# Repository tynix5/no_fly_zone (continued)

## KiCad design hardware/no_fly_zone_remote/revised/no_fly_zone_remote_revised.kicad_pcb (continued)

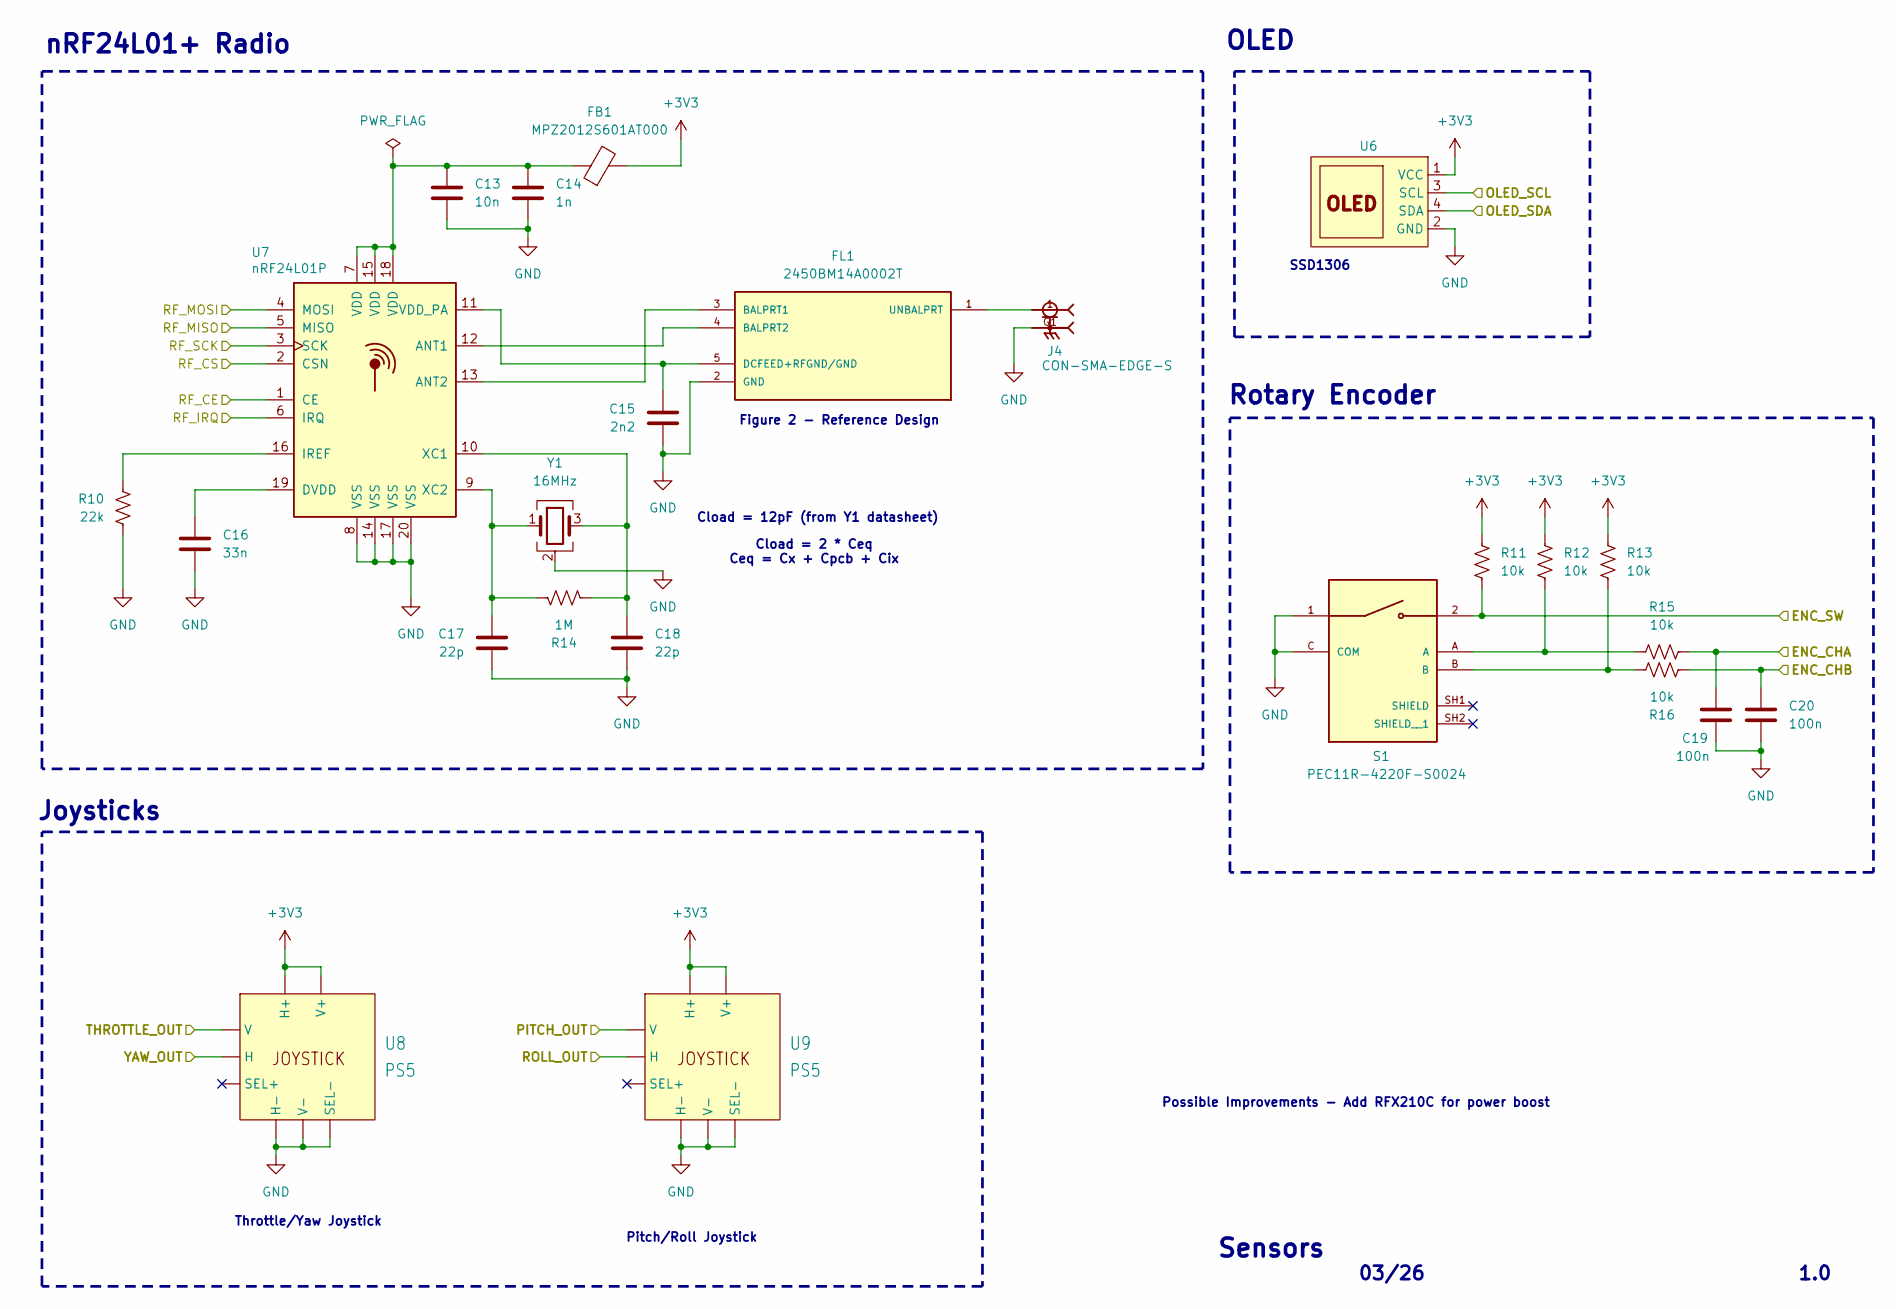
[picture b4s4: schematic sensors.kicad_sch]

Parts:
C13: 10n; C_0402_1005Metric
C14: 1n; C_0402_1005Metric
C15: 2n2; C_0402_1005Metric
C16: 33n; C_0402_1005Metric
C17, C18: 22p; C_0402_1005Metric
C19, C20: 100n; C_0805_2012Metric
FB1: MPZ2012S601AT000; R_0805_2012Metric
FL1: 2450BM14A0002T; FIL_2450BM14A0002T
J4: CON-SMA-EDGE-S; RFSOLUTIONS_CON-SMA-EDGE-S
R10: 22k; R_0402_1005Metric
R11, R12, R13, R15, R16: 10k; R_0805_2012Metric
R14: 1M; R_0402_1005Metric
S1: PEC11R-4220F-S0024; XDCR_PEC11R-4220F-S0024
U6: PinHeader_1x04_P2.54mm_Vertical
U7: nRF24L01P; QFN-20-1EP_4x4mm_P0.5mm_EP2.5x2.5mm
U8, U9: PS5; PS5_Joystick
Y1: 16MHz; XTAL_ABM8AIG-16.000MHZ-12-2Z-T3

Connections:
+3V3: FB1.2, R11.1, R12.1, R13.1, U6.1 (VCC), U8.3 (H+), U8.3' (V+), U9.3 (H+), U9.3' (V+); also elsewhere on the board
/MCU/ADC1_IN7: U9.2' (V); also elsewhere on the board
/MCU/ADC1_IN8: U9.2 (H); also elsewhere on the board
/MCU/ADC1_IN9: U8.2' (V); also elsewhere on the board
/MCU/ADC1_IN16: U8.2 (H); also elsewhere on the board
/MCU/ENC_SW: R11.2, S1.2; also elsewhere on the board
/MCU/I2C1_SCL: U6.3 (SCL); also elsewhere on the board
/MCU/I2C1_SDA: U6.4 (SDA); also elsewhere on the board
/MCU/RF_CE: U7.1 (CE); also elsewhere on the board
/MCU/RF_CS: U7.2 (CSN); also elsewhere on the board
/MCU/RF_IRQ: U7.6 (IRQ); also elsewhere on the board
/MCU/SPI1_MISO: U7.5 (MISO); also elsewhere on the board
/MCU/SPI1_MOSI: U7.4 (MOSI); also elsewhere on the board
/MCU/SPI1_SCK: U7.3 (SCK); also elsewhere on the board
/MCU/TIM2_CH1: C19.1, R15.2; also elsewhere on the board
/MCU/TIM2_CH2: C20.1, R16.1; also elsewhere on the board
GND: C13.2, C14.2, C15.2, C16.2, C17.2, C18.2, C19.2, C20.2, FL1.2 (GND), J4.G1, J4.G2, J4.G3, J4.G4, R10.2, S1.1, S1.C (COM), U6.2 (GND), U7.8 (VSS), U7.14 (VSS), U7.17 (VSS), U7.20 (VSS), U8.1 (H-), U8.1' (V-), U8.c (SEL-), U9.1 (H-), U9.1' (V-), U9.c (SEL-), Y1.2 (G), Y1.4 (G); also elsewhere on the board
unnamed: C13.1, C14.1, FB1.1, U7.7 (VDD), U7.15 (VDD), U7.18 (VDD)
unnamed: FL1.3 (BALPRT1), U7.13 (ANT2)
unnamed: FL1.4 (BALPRT2), U7.12 (ANT1)
unnamed: C15.1, FL1.5 (DCFEED+RFGND/GND), U7.11 (VDD_PA)
unnamed: FL1.1 (UNBALPRT), J4.1
unnamed: R12.2, R15.1, S1.A
unnamed: R13.2, R16.2, S1.B
unnamed: C16.1, U7.19 (DVDD)
unnamed: R10.1, U7.16 (IREF)
unnamed: C18.1, R14.1, U7.10 (XC1), Y1.3
unnamed: C17.1, R14.2, U7.9 (XC2), Y1.1

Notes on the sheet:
03/26
Figure 2 - Reference Design
nRF24L01+ Radio
SSD1306
Rotary Encoder
Cload = 2 * Ceq Ceq = Cx + Cpcb + Cix
Joysticks
Cload = 12pF (from Y1 datasheet)
OLED
1.0
Sensors
Throttle/Yaw Joystick
Pitch/Roll Joystick
Possible Improvements - Add RFX210C for power boost

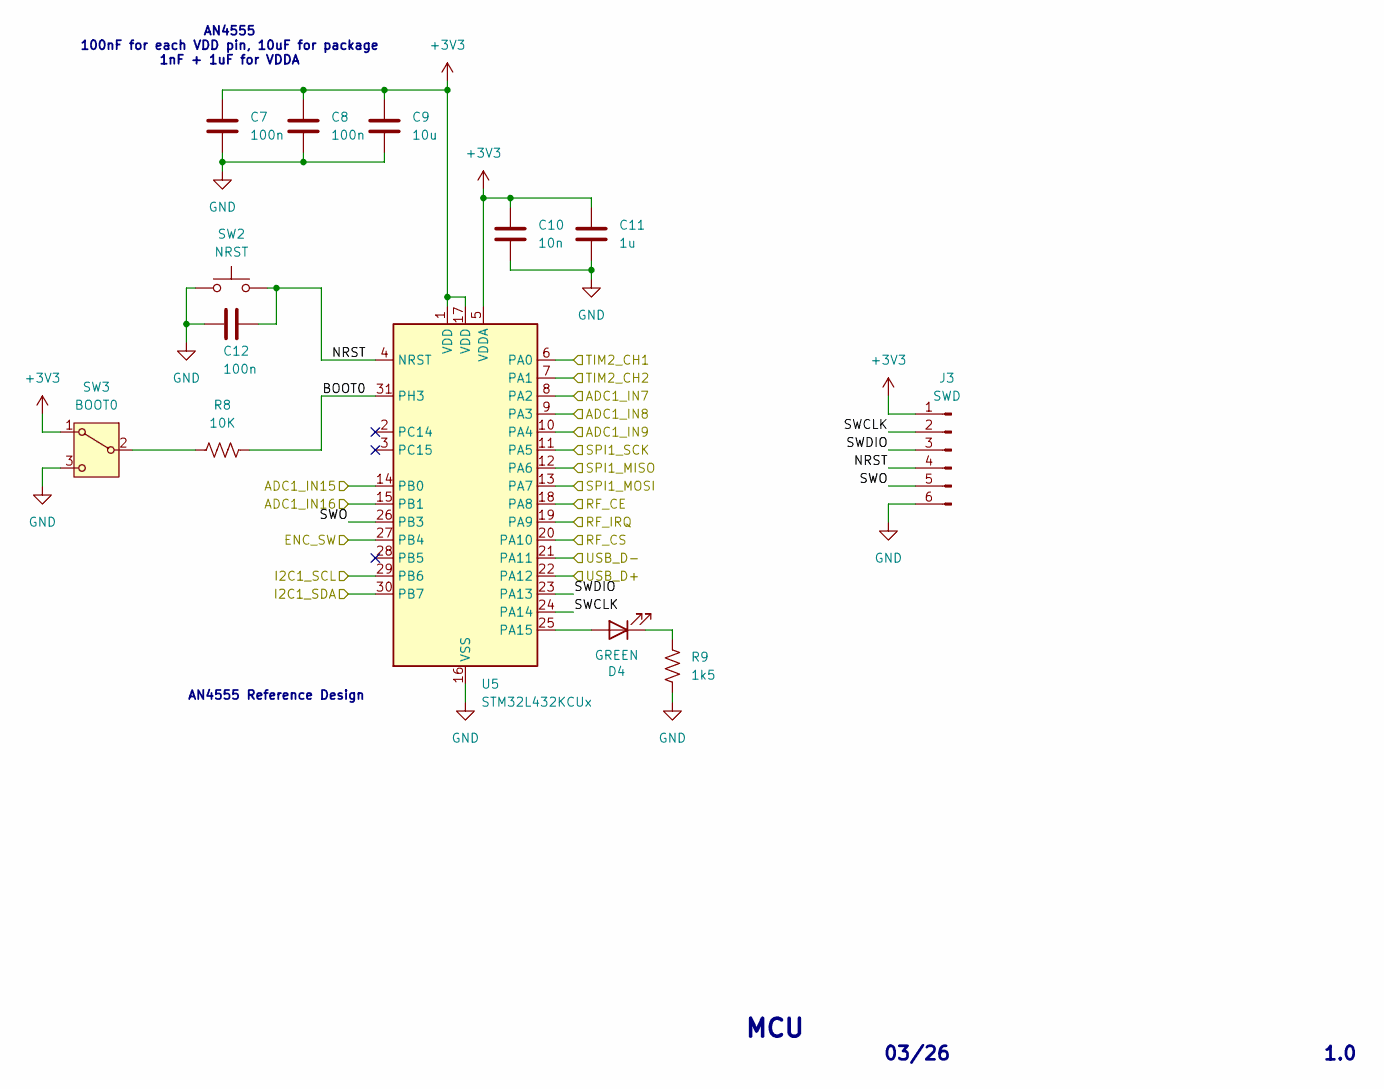
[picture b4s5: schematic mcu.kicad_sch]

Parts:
C7, C8, C12: 100n; C_0805_2012Metric
C9: 10u; C_0805_2012Metric
C10: 10n; C_0805_2012Metric
C11: 1u; C_0805_2012Metric
D4: GREEN; LED_0805_2012Metric
J3: SWD; PinHeader_1x06_P2.54mm_Vertical
R8: 10K; R_0805_2012Metric
R9: 1k5; R_0805_2012Metric
SW2: NRST; SW_SPST_TL3305A
SW3: BOOT0; SW_SPDT_PCM12
U5: STM32L432KCUx; QFN-32-1EP_5x5mm_P0.5mm_EP3.45x3.45mm

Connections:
+3V3: C7.1, C8.1, C9.1, C10.1, C11.1, J3.1, SW3.1 (A), U5.1 (VDD), U5.5 (VDDA), U5.17 (VDD); also elsewhere on the board
/MCU/ADC1_IN7: U5.8 (PA2); also elsewhere on the board
/MCU/ADC1_IN8: U5.9 (PA3); also elsewhere on the board
/MCU/ADC1_IN9: U5.10 (PA4); also elsewhere on the board
/MCU/ADC1_IN15: U5.14 (PB0); also elsewhere on the board
/MCU/ADC1_IN16: U5.15 (PB1); also elsewhere on the board
/MCU/BOOT0: R8.2, U5.31 (PH3)
/MCU/ENC_SW: U5.27 (PB4); also elsewhere on the board
/MCU/I2C1_SCL: U5.29 (PB6); also elsewhere on the board
/MCU/I2C1_SDA: U5.30 (PB7); also elsewhere on the board
/MCU/NRST: C12.1, J3.4, SW2.2, U5.4 (NRST)
/MCU/RF_CE: U5.18 (PA8); also elsewhere on the board
/MCU/RF_CS: U5.20 (PA10); also elsewhere on the board
/MCU/RF_IRQ: U5.19 (PA9); also elsewhere on the board
/MCU/SPI1_MISO: U5.12 (PA6); also elsewhere on the board
/MCU/SPI1_MOSI: U5.13 (PA7); also elsewhere on the board
/MCU/SPI1_SCK: U5.11 (PA5); also elsewhere on the board
/MCU/SWCLK: J3.2, U5.24 (PA14)
/MCU/SWDIO: J3.3, U5.23 (PA13)
/MCU/SWO: J3.5, U5.26 (PB3)
/MCU/TIM2_CH1: U5.6 (PA0); also elsewhere on the board
/MCU/TIM2_CH2: U5.7 (PA1); also elsewhere on the board
/MCU/USB_D+: U5.22 (PA12); also elsewhere on the board
/MCU/USB_D-: U5.21 (PA11); also elsewhere on the board
GND: C7.2, C8.2, C9.2, C10.2, C11.2, C12.2, J3.6, R9.2, SW2.1, SW3.3 (C), U5.16 (VSS), U5.32 (VSS), U5.33 (VSS); also elsewhere on the board
unnamed: D4.2 (A), U5.25 (PA15)
unnamed: D4.1 (K), R9.1
unnamed: R8.1, SW3.2 (B)

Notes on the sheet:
03/26
AN4555 Reference Design
AN4555 100nF for each VDD pin, 10uF for package 1nF + 1uF for VDDA
MCU
1.0

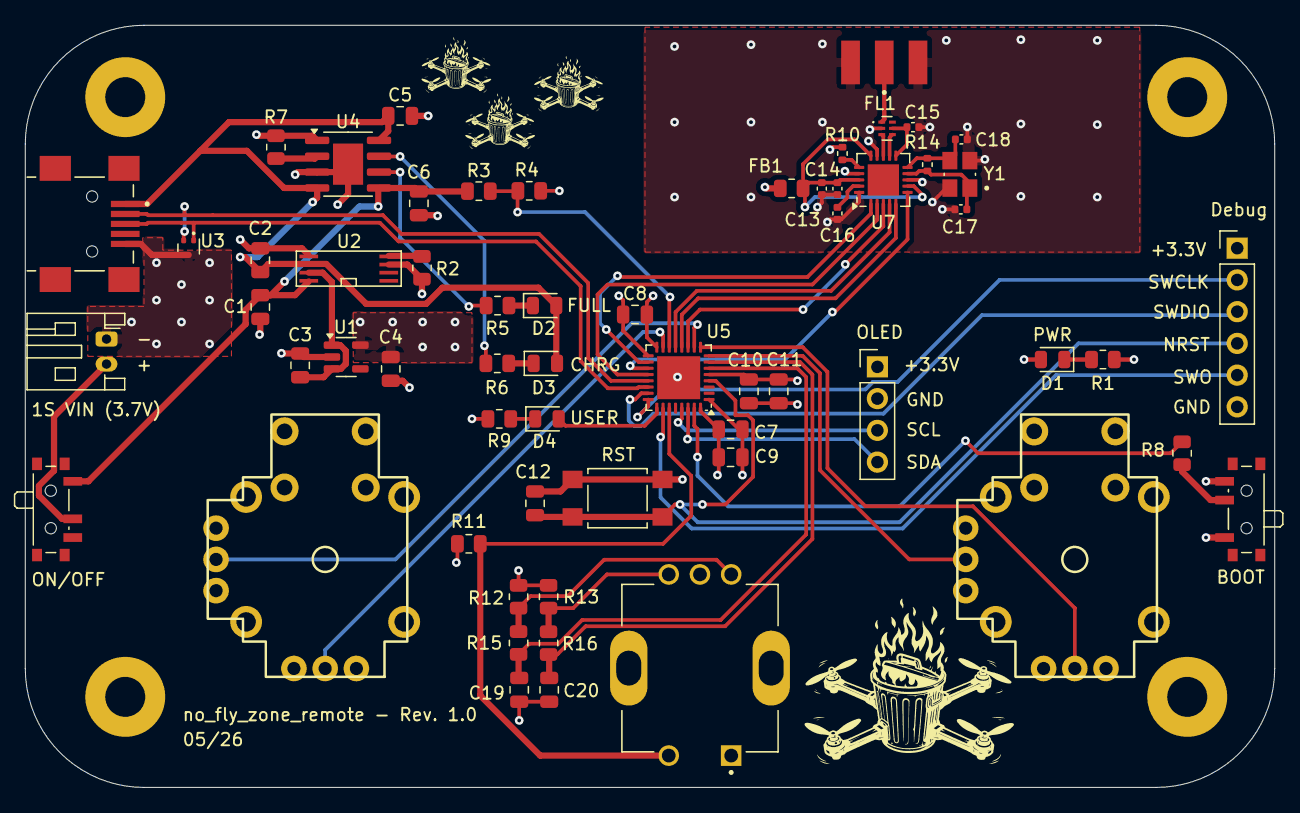
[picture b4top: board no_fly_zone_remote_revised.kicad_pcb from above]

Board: 4 copper layers, 100.0 x 61.0 mm, 64 parts (0 on the bottom side), 50 nets.

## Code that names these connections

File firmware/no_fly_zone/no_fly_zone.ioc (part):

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Mcu.Name=STM32F446R(C-E)Tx
Mcu.Package=LQFP64
Mcu.UserName=STM32F446RCTx
PA0-WKUP.Signal=S_TIM2_CH1_ETR
PA1.Signal=S_TIM5_CH2
PA11.Mode=Device_Only
PA11.Signal=USB_OTG_FS_DM
PA12.Mode=Device_Only
PA12.Signal=USB_OTG_FS_DP
PA13.Mode=Trace_Asynchronous_SW
PA13.Signal=SYS_JTMS-SWDIO
PA14.Mode=Trace_Asynchronous_SW
PA14.Signal=SYS_JTCK-SWCLK
PA15.GPIOParameters=GPIO_Label,GPIO_ModeDefaultEXTI
PA15.GPIO_Label=RF_IRQ
PA15.GPIO_ModeDefaultEXTI=GPIO_MODE_IT_FALLING
PA15.Signal=GPXTI15
PA2.Signal=S_TIM5_CH3
PA3.Signal=S_TIM2_CH4
PA6.GPIOParameters=GPIO_Label
PA6.GPIO_Label=VBAT_SENSE
PA6.Signal=ADCx_IN6
PA7.GPIOParameters=GPIO_Label
PA7.GPIO_Label=CURR_SENSE
PA7.Signal=ADCx_IN7
PA8.GPIOParameters=GPIO_Label
PA8.GPIO_Label=IMU_IRQ1
PA8.Signal=GPXTI8
PA9.GPIOParameters=GPIO_Label
PA9.GPIO_Label=IMU_IRQ2
PA9.Signal=GPXTI9
PB12.GPIOParameters=GPIO_Label
PB12.GPIO_Label=BAR_CS
PB12.Signal=GPIO_Output
PB13.Mode=Full_Duplex_Master
PB13.Signal=SPI2_SCK
PB14.Mode=Full_Duplex_Master
PB14.Signal=SPI2_MISO
PB15.Mode=Full_Duplex_Master
PB15.Signal=SPI2_MOSI
PB3.Mode=Trace_Asynchronous_SW
PB3.Signal=SYS_JTDO-SWO
PB4.GPIOParameters=GPIO_Label
PB4.GPIO_Label=STAT1
PB4.Signal=GPIO_Output
PB5.GPIOParameters=GPIO_Label
PB5.GPIO_Label=STAT2
PB5.Signal=GPIO_Output
PB6.GPIOParameters=GPIO_Label
PB6.GPIO_Label=RF_CS
PB6.Signal=GPIO_Output
PB7.GPIOParameters=GPIO_Label
PB7.GPIO_Label=RF_CE
PB7.Signal=GPIO_Output
PB8.GPIOParameters=GPIO_Label
PB8.GPIO_Label=STAT3
PB8.Signal=GPIO_Output
PC10.Mode=Full_Duplex_Master
PC10.Signal=SPI3_SCK
PC11.Mode=Full_Duplex_Master
PC11.Signal=SPI3_MISO
PC12.Mode=Full_Duplex_Master
PC12.Signal=SPI3_MOSI
PC6.GPIOParameters=GPIO_Label
PC6.GPIO_Label=IMU_CS
PC6.Signal=GPIO_Output
PC7.GPIOParameters=GPIO_Label
PC7.GPIO_Label=BAR_IRQ
PC7.Signal=GPXTI7
PH0-OSC_IN.Mode=HSE-External-Oscillator
PH0-OSC_IN.Signal=RCC_OSC_IN
PH1-OSC_OUT.Mode=HSE-External-Oscillator
PH1-OSC_OUT.Signal=RCC_OSC_OUT
RCC.HSE_VALUE=8000000
RCC.SYSCLKFreq_VALUE=168000000
RCC.SYSCLKSource=RCC_SYSCLKSOURCE_PLLCLK
board=custom

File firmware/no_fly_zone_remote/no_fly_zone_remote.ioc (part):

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Mcu.Name=STM32L432K(B-C)Ux
Mcu.Package=UFQFPN32
Mcu.UserName=STM32L432KCUx
PA0.Signal=S_TIM2_CH1
PA1.Signal=S_TIM2_CH2
PA10.GPIOParameters=GPIO_Label
PA10.GPIO_Label=RF_CS
PA10.Signal=GPIO_Output
PA11.Mode=Device
PA11.Signal=USB_DM
PA12.Mode=Device
PA12.Signal=USB_DP
PA15\ (JTDI).GPIOParameters=GPIO_Label
PA15\ (JTDI).GPIO_Label=USER_LED
PA15\ (JTDI).Signal=GPIO_Output
PA2.GPIOParameters=GPIO_Label
PA2.GPIO_Label=PITCH_ADC
PA2.Signal=ADCx_IN7
PA3.GPIOParameters=GPIO_Label
PA3.GPIO_Label=ROLL_ADC
PA3.Signal=ADCx_IN8
PA4.GPIOParameters=GPIO_Label
PA4.GPIO_Label=THROTTLE_ADC
PA4.Signal=ADCx_IN9
PA5.Mode=Full_Duplex_Master
PA5.Signal=SPI1_SCK
PA6.Mode=Full_Duplex_Master
PA6.Signal=SPI1_MISO
PA7.Mode=Full_Duplex_Master
PA7.Signal=SPI1_MOSI
PA8.GPIOParameters=GPIO_Label
PA8.GPIO_Label=RF_CE
PA8.Signal=GPIO_Output
PA9.GPIOParameters=GPIO_Label
PA9.GPIO_Label=RF_IRQ
PA9.Signal=GPIO_Input
PB0.GPIOParameters=GPIO_Label
PB0.GPIO_Label=BATT_LVL
PB0.Signal=ADCx_IN15
PB1.GPIOParameters=GPIO_Label
PB1.GPIO_Label=YAW_ADC
PB1.Signal=ADCx_IN16
PB4\ (NJTRST).GPIOParameters=GPIO_Label
PB4\ (NJTRST).GPIO_Label=ENC_SW
PB4\ (NJTRST).Signal=GPIO_Input
PB6.GPIOParameters=GPIO_Pu
PB6.GPIO_Pu=GPIO_NOPULL
PB6.Mode=I2C
PB6.Signal=I2C1_SCL
PB7.GPIOParameters=GPIO_Pu
PB7.GPIO_Pu=GPIO_NOPULL
PB7.Mode=I2C
PB7.Signal=I2C1_SDA
RCC.HSE_VALUE=8000000
RCC.SYSCLKFreq_VALUE=80000000
RCC.SYSCLKSource=RCC_SYSCLKSOURCE_PLLCLK
board=custom

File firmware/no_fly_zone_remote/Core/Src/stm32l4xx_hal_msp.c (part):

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    __HAL_RCC_GPIOA_CLK_ENABLE();
    __HAL_RCC_GPIOB_CLK_ENABLE();
    /**ADC1 GPIO Configuration
    PA2     ------> ADC1_IN7
    PA3     ------> ADC1_IN8
    PA4     ------> ADC1_IN9
    PB0     ------> ADC1_IN15
    PB1     ------> ADC1_IN16
    */
    GPIO_InitStruct.Pin = PITCH_ADC_Pin|ROLL_ADC_Pin|THROTTLE_ADC_Pin;
    GPIO_InitStruct.Mode = GPIO_MODE_ANALOG_ADC_CONTROL;
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    __HAL_RCC_ADC_CLK_DISABLE();

    /**ADC1 GPIO Configuration
    PA2     ------> ADC1_IN7
    PA3     ------> ADC1_IN8
    PA4     ------> ADC1_IN9
    PB0     ------> ADC1_IN15
    PB1     ------> ADC1_IN16
    */
    HAL_GPIO_DeInit(GPIOA, PITCH_ADC_Pin|ROLL_ADC_Pin|THROTTLE_ADC_Pin);

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
    __HAL_RCC_GPIOB_CLK_ENABLE();
    /**I2C1 GPIO Configuration
    PB6     ------> I2C1_SCL
    PB7     ------> I2C1_SDA
    */
    GPIO_InitStruct.Pin = GPIO_PIN_6|GPIO_PIN_7;
    GPIO_InitStruct.Mode = GPIO_MODE_AF_OD;
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    __HAL_RCC_I2C1_CLK_DISABLE();

    /**I2C1 GPIO Configuration
    PB6     ------> I2C1_SCL
    PB7     ------> I2C1_SDA
    */
    HAL_GPIO_DeInit(GPIOB, GPIO_PIN_6);

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
    __HAL_RCC_GPIOA_CLK_ENABLE();
    /**SPI1 GPIO Configuration
    PA5     ------> SPI1_SCK
    PA6     ------> SPI1_MISO
    PA7     ------> SPI1_MOSI
    */
    GPIO_InitStruct.Pin = GPIO_PIN_5|GPIO_PIN_6|GPIO_PIN_7;
    GPIO_InitStruct.Mode = GPIO_MODE_AF_PP;
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    __HAL_RCC_SPI1_CLK_DISABLE();

    /**SPI1 GPIO Configuration
    PA5     ------> SPI1_SCK
    PA6     ------> SPI1_MISO
    PA7     ------> SPI1_MOSI
    */
    HAL_GPIO_DeInit(GPIOA, GPIO_PIN_5|GPIO_PIN_6|GPIO_PIN_7);

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
    __HAL_RCC_GPIOA_CLK_ENABLE();
    /**TIM2 GPIO Configuration
    PA0     ------> TIM2_CH1
    PA1     ------> TIM2_CH2
    */
    GPIO_InitStruct.Pin = GPIO_PIN_0|GPIO_PIN_1;
    GPIO_InitStruct.Mode = GPIO_MODE_AF_PP;
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    __HAL_RCC_TIM2_CLK_DISABLE();

    /**TIM2 GPIO Configuration
    PA0     ------> TIM2_CH1
    PA1     ------> TIM2_CH2
    */
    HAL_GPIO_DeInit(GPIOA, GPIO_PIN_0|GPIO_PIN_1);

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
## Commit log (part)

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2026-04-14 Added README.md
2026-04-14 Added submodule for nrf24l01
2026-04-15 Baremetal NRF24L01 testing. Needs to be tested on hardware
2026-04-15 Removed ignored files from tracking
2026-04-16 Separated drivers from main application
2026-04-16 Added stm32 submodules
2026-04-16 Updated submodules
2026-04-16 Using HAL Drivers for all peripherals. Updated submodules
2026-04-18 Initial successful radio communication
2026-04-19 Added new configuration parameters. Dynamic lengths with no acks has been tested
2026-04-19 Working dynamic ack with payload configuration
2026-04-27 Modified makefiles to point to local stm32_lib
2026-05-27 Tested radio functionality and added blink tests. Radio communication successful
2026-05-27 Added ADC + DMA functionality with interrupts. Adding OLED library for displaying relevant information
2026-05-27 Added OLED pages for battery and joystick states. Need to test with rotary encoder for menu changes
2026-06-01 Added encoder logic to move between menus. Moved all OLED functions to separate helper file. Updated submodules
2026-06-08 Modified pin layouts to match PCB and currently testing EXTI functionality with nRF and IMU
2026-06-08 Added OLED helper functions for drawing visuals on display. Need to reduce update time
2026-06-11 Revision 1.0 of remote control and quadcopter MCU + sensor board added. Remote PCB is functional, quadcopter boards need to be tested
2026-06-11 Added READMEs for hardware sections and updated parts.txt
2026-06-11 Updated top-level README
2026-06-23 Tested nRF24L01 functionality on custom quadcopter PCB successfully
2026-06-23 Updated READMEs
2026-06-24 Added sensor library paths
2026-06-24 Successfully tested barometer, imu, and rf interrupts
